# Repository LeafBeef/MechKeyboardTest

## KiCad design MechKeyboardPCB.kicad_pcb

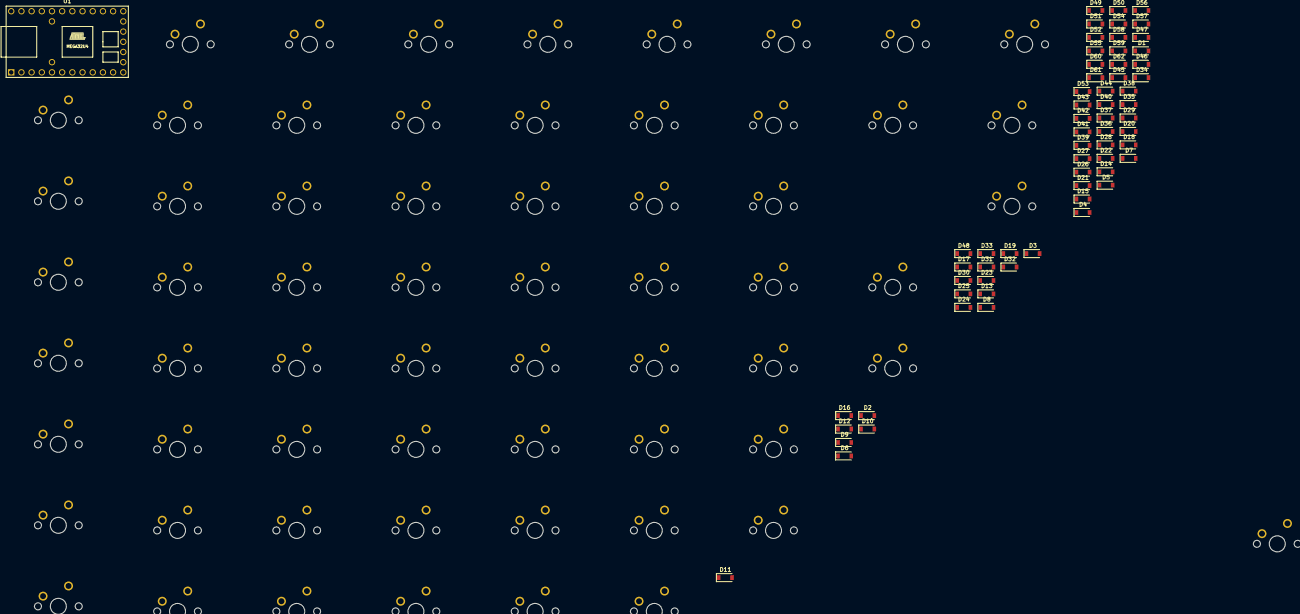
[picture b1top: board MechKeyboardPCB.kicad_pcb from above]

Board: 2 copper layers, 125 parts (0 on the bottom side), 81 nets, no tracks yet.

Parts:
D1, D2, D3, D4, D5, D6, D7, D8, D9, D10, D11, D12, D13, D14, D15, D16, D17, D18, D19, D20, D21, D22, D23, D24, D25, D26, D27, D28, D29, D30, D31, D32, D33, D34, D35, D36, D37, D38, D39, D40, D41, D42, D43, D44, D45, D46, D47, D48, D49, D50, D51, D52, D53, D54, D55, D56, D57, D58, D59, D60, D61, D62: D; D_SOD-123
MX1, MX2, MX3, MX4, MX5, MX6, MX7, MX8, MX9, MX10, MX11, MX12, MX13, MX14, MX15, MX16, MX17, MX18, MX19, MX20, MX21, MX22, MX23, MX24, MX25, MX26, MX27, MX28, MX29, MX30, MX31, MX32, MX33, MX34, MX35, MX36, MX37, MX38, MX39, MX40, MX41, MX42, MX43, MX44, MX45, MX46, MX47, MX48, MX49, MX50, MX51, MX52, MX53, MX54, MX55, MX56, MX57, MX58, MX59, MX60, MX61, MX62: MX-NoLED; MXOnly-1.5U-NoLED
U1: Teensy2.0_(Arduino); Teensy2.0

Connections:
unnamed: D1.1, D2.1, D3.1, D4.1, D5.1, U1.20
unnamed: D1.2, MX1.1
unnamed: D2.2, MX2.1
unnamed: D3.2, MX3.1
unnamed: D4.2, MX4.1
unnamed: D5.2, MX5.1
unnamed: D6.2, MX6.1
unnamed: D7.2, MX7.1
unnamed: D8.2, MX8.1
unnamed: D9.2, MX9.1
unnamed: D6.1, D7.1, D8.1, D9.1, D10.1, U1.21
unnamed: D10.2, MX10.1
unnamed: D11.1, D12.1, D13.1, D14.1, D15.1, U1.22
unnamed: D11.2, MX11.1
unnamed: D12.2, MX12.1
unnamed: D13.2, MX13.1
unnamed: D14.2, MX14.1
unnamed: D15.2, MX15.1
unnamed: D16.1, D17.1, D18.1, D19.1, U1.23
unnamed: D16.2, MX16.1
unnamed: D17.2, MX17.1
unnamed: D18.2, MX18.1
unnamed: D19.2, MX19.1
unnamed: D20.1, D21.1, D22.1, D23.1, U1.24
unnamed: D20.2, MX20.1
unnamed: D21.2, MX21.1
unnamed: D22.2, MX22.1
unnamed: D23.2, MX23.1
unnamed: D24.1, D25.1, D26.1, D27.1, U1.25
unnamed: D24.2, MX24.1
unnamed: D25.2, MX25.1
unnamed: D26.2, MX26.1
unnamed: D27.2, MX27.1
unnamed: D28.1, D29.1, D30.1, D31.1, D32.1, U1.26
unnamed: D28.2, MX28.1
unnamed: D29.2, MX29.1
unnamed: D30.2, MX30.1
unnamed: D31.2, MX31.1
unnamed: D32.2, MX32.1
unnamed: D33.1, D34.1, D35.1, D36.1, U1.27
unnamed: D33.2, MX33.1
unnamed: D34.2, MX34.1
unnamed: D35.2, MX35.1
unnamed: D36.2, MX36.1
unnamed: D37.1, D38.1, D39.1, D40.1, U1.28
unnamed: D37.2, MX37.1
unnamed: D38.2, MX38.1
unnamed: D39.2, MX39.1
unnamed: D40.2, MX40.1
unnamed: D41.1, D42.1, D43.1, D44.1, U1.12
unnamed: D41.2, MX41.1
unnamed: D42.2, MX42.1
unnamed: D43.2, MX43.1
unnamed: D44.2, MX44.1
unnamed: D45.1, D46.1, D47.1, D48.1, D49.1, U1.11
unnamed: D45.2, MX45.1
unnamed: D46.2, MX46.1
unnamed: D47.2, MX47.1
unnamed: D48.2, MX48.1
unnamed: D49.2, MX49.1
unnamed: D50.1, D51.1, D52.1, D53.1, D54.1, U1.10
unnamed: D50.2, MX50.1
unnamed: D51.2, MX51.1
unnamed: D52.2, MX52.1
unnamed: D53.2, MX53.1
unnamed: D54.2, MX54.1
unnamed: D55.1, D56.1, D57.1, D58.1, D59.1, U1.9
unnamed: D55.2, MX55.1
unnamed: D56.2, MX56.1
unnamed: D57.2, MX57.1
unnamed: D58.2, MX58.1
unnamed: D59.2, MX59.1
unnamed: D60.1, D61.1, D62.1, U1.8
unnamed: D60.2, MX60.1
unnamed: D61.2, MX61.1
unnamed: D62.2, MX62.1
unnamed: MX1.2, MX6.2, MX11.2, MX16.2, MX20.2, MX24.2, MX28.2, MX33.2, MX37.2, MX41.2, MX45.2, MX50.2, MX55.2, MX60.2, U1.6
unnamed: MX5.2, MX10.2, MX15.2, MX32.2, MX49.2, MX54.2, MX59.2, MX62.2, U1.2
unnamed: MX2.2, MX7.2, MX12.2, MX17.2, MX21.2, MX25.2, MX29.2, MX34.2, MX38.2, MX42.2, MX46.2, MX51.2, MX56.2, MX61.2, U1.5
unnamed: MX3.2, MX8.2, MX13.2, MX18.2, MX22.2, MX26.2, MX30.2, MX35.2, MX39.2, MX43.2, MX47.2, MX52.2, MX57.2, U1.4
unnamed: MX4.2, MX9.2, MX14.2, MX19.2, MX23.2, MX27.2, MX31.2, MX36.2, MX40.2, MX44.2, MX48.2, MX53.2, MX58.2, U1.3

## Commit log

2021-01-27 Initialize Project
2021-01-27 Test V1
    Layout nicht zufrieden, muss alles überarbeiten wahrscheinlich neu anfangen
